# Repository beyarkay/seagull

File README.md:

# Conway's Game of Life (entirely in hardware)

> NOTE:
>
> This is a KiCAD project, don't expect GitHub to play especially well with it.

|   Back Copper Layer    |    Front Copper Layer    |
| :--------------------: | :----------------------: |
|  |  |

This project implements Conway's game of life, entirely in hardware. Many
existing attempts to do this fail (IMO) in one of several ways. The features of
this project are:

- All logic is computed via logic gates, no microcontrollers are used
- Each cell in the game of life is an independent PCB, and cells can be
  disconnected/connected at will

I am still busy optimising the design, but I have ordered and tested PCBs from
JLCPCB, the design and concept works.

|      Input/Output Headers      |
| :----------------------------: |
|              |
|       Sum-of-neighbours        |
|  |
|   Logic (should I be dead?)    |
|        |

# What is Conway's Game of Life?

(expand if you don't know what CGoL is)

<summary>
<details>
It is a cellular automaton on an infinite grid of square cells. Each cell is
either alive or dead. All cells update **simultaneously** in discrete ticks
based only on their eight adjacent neighbours (N, NE, E, SE, S, SW, W, NW). It
is usually called a **zero-player** game: you choose the starting pattern; the
rules determine everything after.

Rules per tick:

- exactly three live neighbours => the cell is alive next tick (birth or survival)
- exactly two live neighbours **and** the cell is currently alive => it stays alive
- any other neighbours count => the cell is dead next tick

This small rule set yields rich behaviour:

- Still lifes: patterns that do not change (e.g., block, beehive)
- Oscillators: patterns that repeat after N ticks (e.g., blinker, toad)
- Spaceships: patterns that translate over the grid (e.g., glider)
- Guns: patterns that periodically emit spaceships (e.g., Gosper glider gun)

Example of motion and emission:

There is a large taxonomy of creatures in CGoL, the [wiki][1] is comprehensive.

</details>
</summary>

# What is this project?

This project is a circuit board that implements Conway's game of life in pure
hardware using digital logic circuits. There is no Arduino, no code, no
microcontrollers, no "flashing". Just NOR gates. Each cell in Game of Life is a
completely independent PCB, and only has knowledge of it's eight immediate
neighbours. Physically connecting a grid of PCBs together will give you a
network of cells, and then you can run Game of Life.

|  Render of the front of the PCB   |  Render of the back of the PCB  |
| :-------------------------------: | :-----------------------------: |
|  |  |

As far as I can tell, nobody's done this before. There's been hardware
implementations of Life, but they all use microcontrollers and typically just
have one small grid that can't be extended (which seems lame IMO).

Each cell is about 35mm on a side and has an LED in the middle to indicate if
the cell is alive or dead. There's also two buttons: KILL and REVIVE that'll
force the state of the cell, so that you can initialise the game.

|    Two cells connected together     | Render of many cells connected together |
| :---------------------------------: | :-------------------------------------: |
|  |   |

I'm quite proud of this little thing. It's the first PCB I've designed and
overall it went really well. There were several fun engineering challenges with
routing information between cells and minimising the Game of Life logic to be
suitable for expression via NOR gates. My background is in the ideal perfect
world of computer science, and it has been very interesting learning PCB design
and making something that works in the real world against real constraints. I
strongly recommend anyone curious about it to give PCB design a go.

| It works! (cell in a testing jig, in the "alive" state) |
| :-----------------------------------------------------: |
|                     |

# Challenges/details

(I'm still writing this up and adding to this as I encounter new challenges)

## Routing information between cells

Each cell needs to know the state (alive/dead) of the eight cells surrounding
it. The four directly adjacent cells are easy, we can just have a pin & socket
poking out of the four edges of the boards. But the four diagonal cells are
trickier, because if we had diagonal pins & sockets then we wouldn't be able to
plug anything in.

The solution here is quite neat: you can route the information for diagonal
cells _through_ the directly adjacent cells. For example, to get state from the
top-left cell to the central cell, the state for the top-left cell will go
first to the left cell, and then to the central cell.

| Cell State is communicated via adjacent neighbours |
| :------------------------------------------------: |
|                                  |

## Implementing Game of Life via NOR circuits

(WIP)

## Calculating the neighbours sum

(WIP)

## Problems & frustrations

[you-live-like-this.meme]

Some notes from a software dev about pains in the electronic engineering world
that absolutely don't need to be there. It's kinda insane to me that some of
these problems still exist and don't have _any_ prospective solutions.

- PCB circuit "linting" basically doesn't exist, and could be a lot better.
- importing footprints is incredibly tedious and manual, not at all like `cargo
add random`.
- Insane that circuit manufacturers almost certainly have computer-readable
  descriptions of the behaviour of their chips but don't make that generally
  available. If you want to run "unit tests" on your circuit, you basically
  have to mock/re-define the behaviour of every chip you use. Which is a mammoth
  task if starting from scratch.
- The datasheet is the medium for communicating information about electrical
  components, but _there's no computer-readable format_. So you end up having
  to also find some footprints and schematics for the component (this
  information is in the datasheet, but computer's can't parse the
  images/diagrams).
- KiCAD is (mostly) a very capable piece of software. It could be better, but
  all my problems are "wants" rather than "needs", and I never explored the
  ecosystem of plugins that I believe dramatically improve the base experience.

To be clear: lots of these problems are "small" or "once-off" or solvable by
"just know this hack". But the whole culture in electronic engineering seems to
be to ignore the paper-cuts, while the culture amongst software engineers is
overwhelmingly the opposite. Software engineers are probably more guilty of
spending too _much_ time trying to automate every little inconvenience and
remove all manual steps from their once-a-year workflow. But the result of this
obsession is that most things are _able_ to be automated, and there's a
proliferation of adhered-to standards. Critically, being able to automate
things requires well-defined interfaces between different companies &
organisations across different countries. We tend to take this for granted in
software, especially amongst open-source. But electrical engineers remark that
certain automation steps are impossible because it requires coordination across
different suppliers on standards for representing information about components.
This is 100% a solved problem in software, and I'd never before realised what a
powerhouse the humble RFC is. The lack of a computer-readable datasheet for
electrical components is _insane_ to me, and ripe for automation via LLMs (if
not today, then in 5 years time).

# Next steps

Thanks to the Albert, Karel, Dirk S., Armand, and the other devs at CubeSpace
for advice, and various anime-profile-picture twitter accounts in the PCB Book
Club for schematic/PCB reviews)

[1]: https://conwaylife.com/wiki/Main_Page

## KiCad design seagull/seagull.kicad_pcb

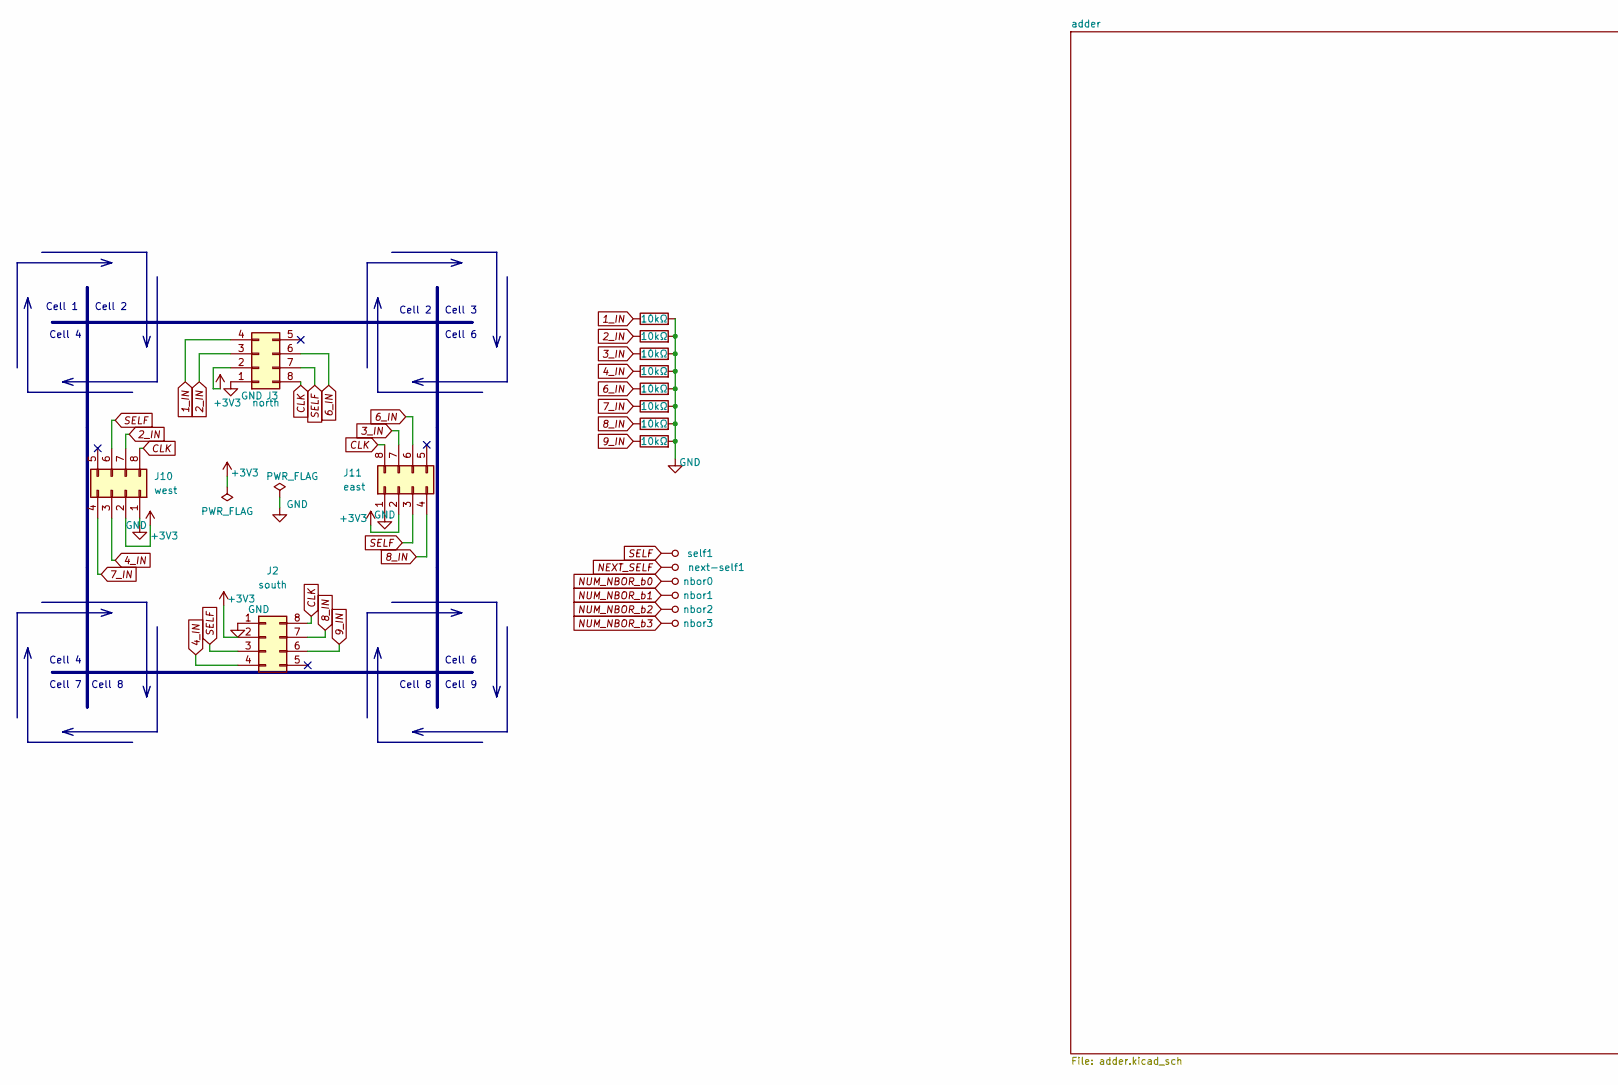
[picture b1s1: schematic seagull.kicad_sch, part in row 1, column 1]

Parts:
J2: south; PinHeader_2x04_P2.54mm_Horizontal
J3: north; PinSocket_2x04_P2.54mm_Horizontal
J10: west; PinSocket_2x04_P2.54mm_Horizontal
J11: east; PinHeader_2x04_P2.54mm_Horizontal
R1, R2, R3, R4, R5, R6, R7, R8: 10kΩ; R_1206_3216Metric_Pad1.30x1.75mm_HandSolder
nbor0, nbor1, nbor2, nbor3: 5011; TestPoint_Pad_D1.0mm; MPN 5011; Digi-Key_PN 36-5011-ND
next-self1: 5011; TestPoint_Pad_D1.0mm; MPN 5011; Digi-Key_PN 36-5011-ND
self1: 5011; TestPoint_Pad_D1.0mm; MPN 5011; Digi-Key_PN 36-5011-ND

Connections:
1_IN: J3.4, R1.1; also elsewhere on the board
2_IN: J3.3, J10.7, R2.1; also elsewhere on the board
3_IN: J11.7, R3.1; also elsewhere on the board
4_IN: J2.4, J10.3, R4.1; also elsewhere on the board
6_IN: J3.6, J11.6, R5.1; also elsewhere on the board
7_IN: J10.4, R6.1; also elsewhere on the board
8_IN: J2.7, J11.4, R7.1; also elsewhere on the board
9_IN: J2.6, R8.1; also elsewhere on the board
CLK: J2.8, J3.8, J10.8, J11.8; also elsewhere on the board
GND: J2.1, J3.1, J10.1, J11.1, R1.2, R2.2, R3.2, R4.2, R5.2, R6.2, R7.2, R8.2; also elsewhere on the board
NEXT_SELF: next-self1.1; also elsewhere on the board
NUM_NBOR_b0: nbor0.1; also elsewhere on the board
NUM_NBOR_b1: nbor1.1; also elsewhere on the board
NUM_NBOR_b2: nbor2.1; also elsewhere on the board
NUM_NBOR_b3: nbor3.1; also elsewhere on the board
SELF: J2.3, J3.7, J10.6, J11.3, self1.1; also elsewhere on the board

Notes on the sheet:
Cell 4
Cell 3
Cell 6
Cell 8
Cell 7
Cell 9
Cell 1
Cell 2

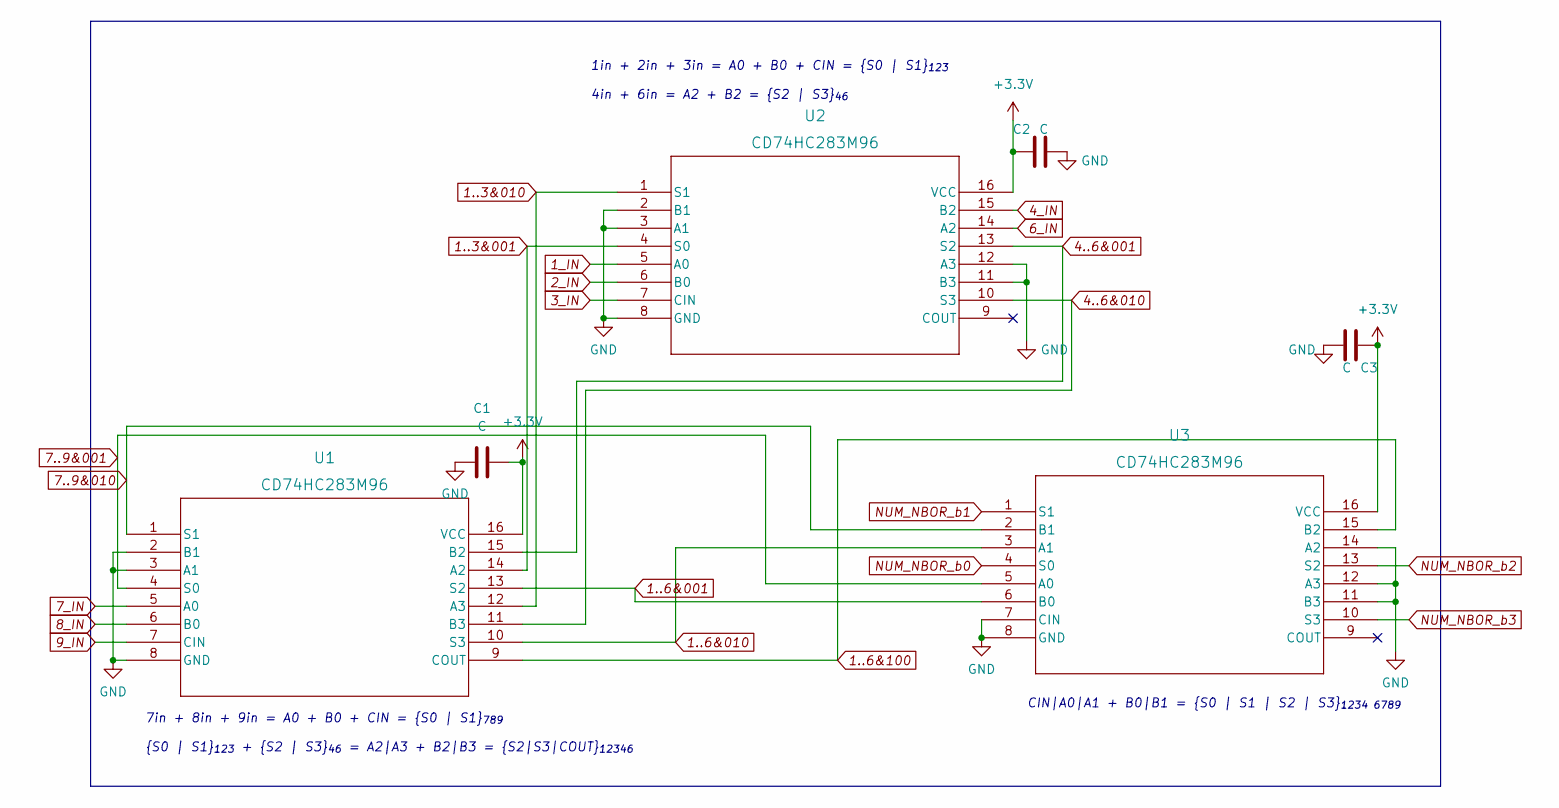
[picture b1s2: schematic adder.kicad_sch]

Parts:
C1, C2, C3: C; C_1206_3216Metric_Pad1.33x1.80mm_HandSolder
U1, U2, U3: CD74HC283M96; CD74HC283M96_4bit_adder_D16-L

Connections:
1..3&001: U1.14 (A2), U2.4 (S0)
1..3&010: U1.12 (A3), U2.1 (S1)
1..6&001: U1.13 (S2), U3.6 (B0)
1..6&010: U1.10 (S3), U3.3 (A1)
1..6&100: U1.9 (COUT), U3.15 (B2)
1_IN: U2.5 (A0); also elsewhere on the board
2_IN: U2.6 (B0); also elsewhere on the board
3_IN: U2.7 (CIN); also elsewhere on the board
4..6&001: U1.15 (B2), U2.13 (S2)
4..6&010: U1.11 (B3), U2.10 (S3)
4_IN: U2.15 (B2); also elsewhere on the board
6_IN: U2.14 (A2); also elsewhere on the board
7..9&001: U1.4 (S0), U3.5 (A0)
7..9&010: U1.1 (S1), U3.2 (B1)
7_IN: U1.5 (A0); also elsewhere on the board
8_IN: U1.6 (B0); also elsewhere on the board
9_IN: U1.7 (CIN); also elsewhere on the board
GND: C1.1, C2.2, C3.2, U1.2 (B1), U1.3 (A1), U1.8 (GND), U2.2 (B1), U2.3 (A1), U2.8 (GND), U2.11 (B3), U2.12 (A3), U3.7 (CIN), U3.8 (GND), U3.11 (B3), U3.12 (A3), U3.14 (A2); also elsewhere on the board
NUM_NBOR_b0: U3.4 (S0); also elsewhere on the board
NUM_NBOR_b1: U3.1 (S1); also elsewhere on the board
NUM_NBOR_b2: U3.13 (S2); also elsewhere on the board
NUM_NBOR_b3: U3.10 (S3); also elsewhere on the board

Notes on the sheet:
CIN|A0|A1 + B0|B1 = {S0 | S1 | S2 | S3}_{1234 6789}
1in + 2in + 3in = A0 + B0 + CIN = {S0 | S1}_{123} 4in + 6in = A2 + B2 = {S2 | S3}_{46}
7in + 8in + 9in = A0 + B0 + CIN = {S0 | S1}_{789} {S0 | S1}_{123} + {S2 | S3}_{46} = A2|A3 + B2|B3 = {S2|S3|COUT}_{12346}

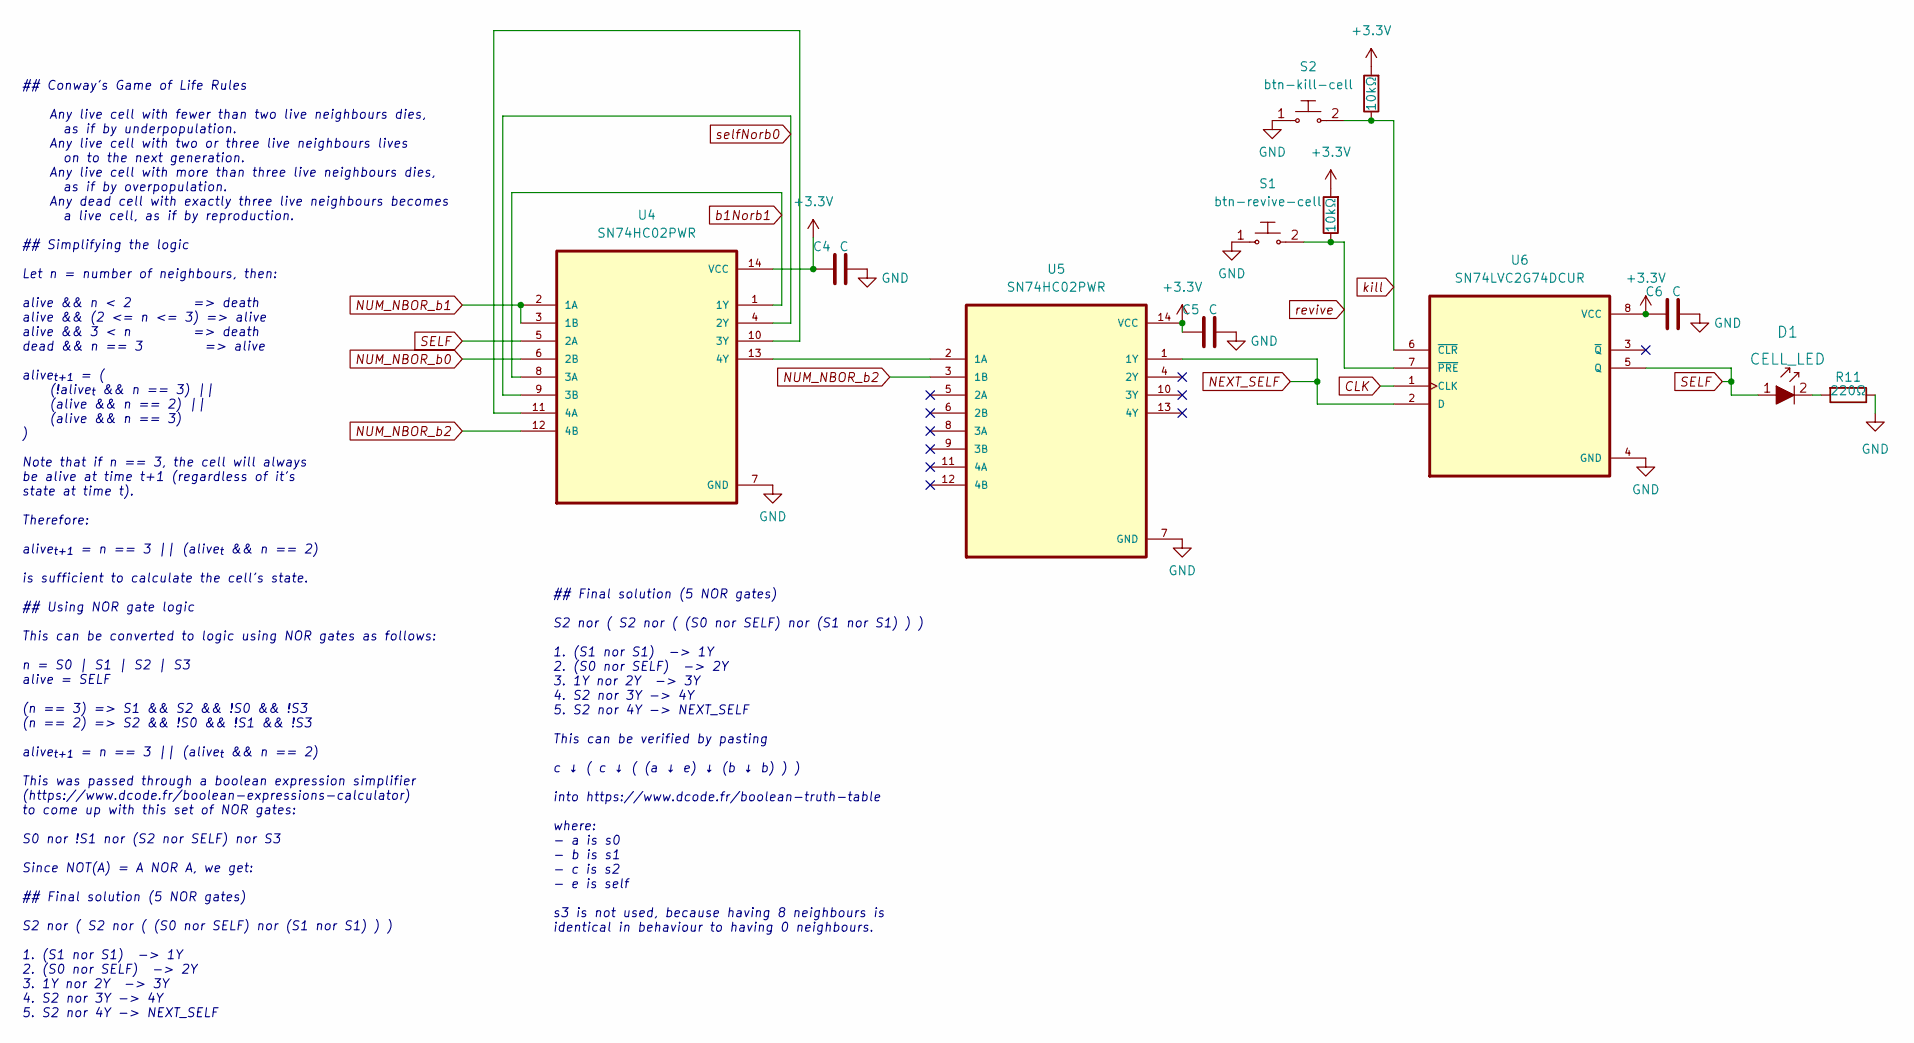
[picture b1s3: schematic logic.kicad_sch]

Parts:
C4, C5, C6: C; C_1206_3216Metric_Pad1.33x1.80mm_HandSolder
D1: CELL_LED; 1206; MPN LTST-C171KRKT; Digi-Key_PN 160-1427-1-ND
R9, R10: 10kΩ; R_1206_3216Metric_Pad1.30x1.75mm_HandSolder
R11: 220Ω; R_1206_3216Metric_Pad1.30x1.75mm_HandSolder
S1: btn-revive-cell; SW_1825910-6-btn; MPN GPTS203211B; Digi-Key_PN CW181-ND
S2: btn-kill-cell; SW_1825910-6-btn; MPN GPTS203211B; Digi-Key_PN CW181-ND
U4, U5: SN74HC02PWR; SN74HC02PWR_NOR_4CH_2-INP
U6: SN74LVC2G74DCUR; SN74LVC2G74DCUR_d-flip-flop

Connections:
CLK: U6.1 (CLK); also elsewhere on the board
GND: C4.2, C5.2, C6.2, R11.1, S1.1, S2.1, U4.7 (GND), U5.7 (GND), U6.4 (GND); also elsewhere on the board
NEXT_SELF: U5.1 (1Y), U6.2 (D); also elsewhere on the board
NUM_NBOR_b0: U4.6 (2B); also elsewhere on the board
NUM_NBOR_b1: U4.2 (1A), U4.3 (1B); also elsewhere on the board
NUM_NBOR_b2: U4.12 (4B), U5.3 (1B); also elsewhere on the board
unnamed: D1.2, R11.2
unnamed: U4.10 (3Y), U4.11 (4A)
unnamed: U4.13 (4Y), U5.2 (1A)
SELF: D1.1, U4.5 (2A), U6.5 (Q); also elsewhere on the board
b1Norb1: U4.1 (1Y), U4.8 (3A)
kill: R10.1, S2.2, U6.6 (~CLR)
revive: R9.1, S1.2, U6.7 (~PRE)
selfNorb0: U4.4 (2Y), U4.9 (3B)

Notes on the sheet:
## Conway's Game of Life Rules Any live cell with fewer than two live neighbours dies, as if by underpopulation. Any live cell with two or three live neighbours lives on to the next generation. Any live cell with more than three live neighbours dies, as if by overpopulation. Any dead cell with exac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
## Final solution (5 NOR gates) S2 nor ( S2 nor ( (S0 nor SELF) nor (S1 nor S1) ) ) 1. (S1 nor S1) -> 1Y 2. (S0 nor SELF) -> 2Y 3. 1Y nor 2Y -> 3Y 4. S2 nor 3Y -> 4Y 5. S2 nor 4Y -> NEXT_SELF This can be verified by pasting c ↓ ( c ↓ ( (a ↓ e) ↓ (b ↓ b) ) ) into https://www.dcode.fr/boolean-truth-t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

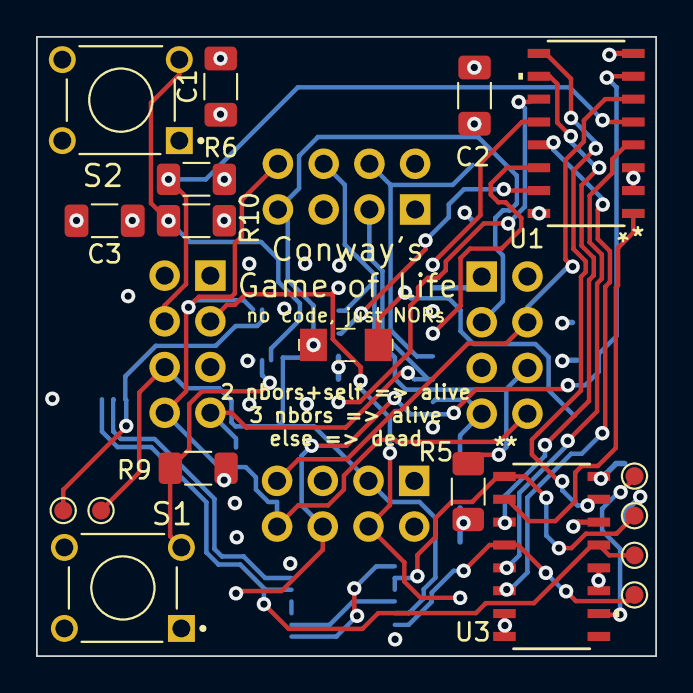
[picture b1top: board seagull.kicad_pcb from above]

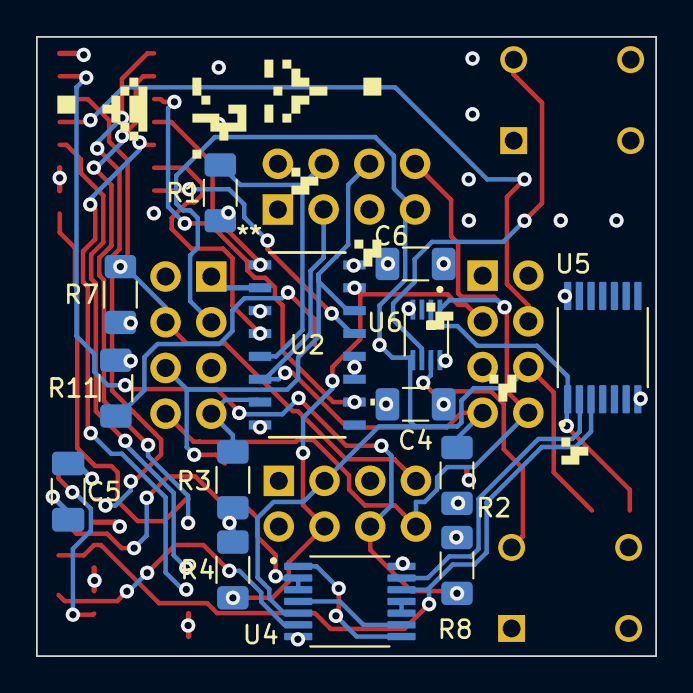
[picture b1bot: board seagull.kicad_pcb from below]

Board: 4 copper layers, 34.4 x 34.4 mm, 36 parts (14 on the bottom side), 33 nets.

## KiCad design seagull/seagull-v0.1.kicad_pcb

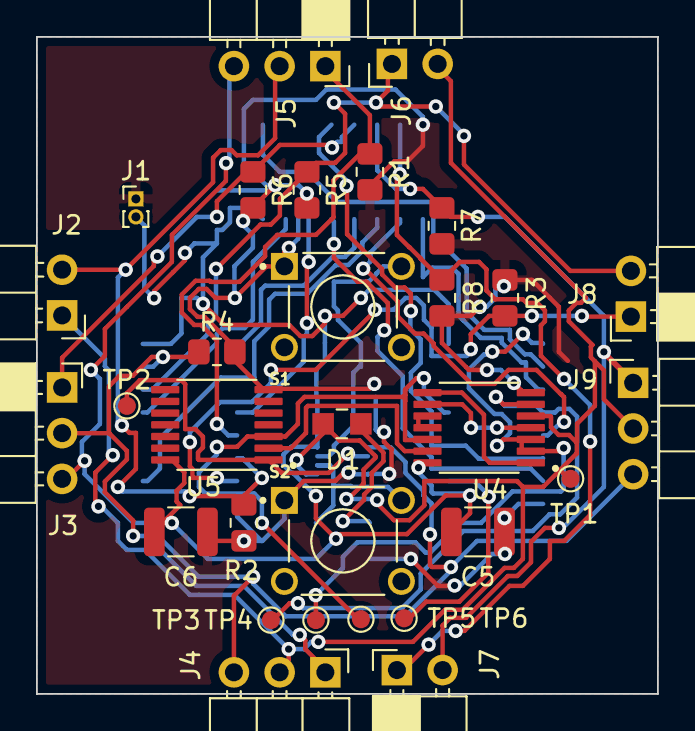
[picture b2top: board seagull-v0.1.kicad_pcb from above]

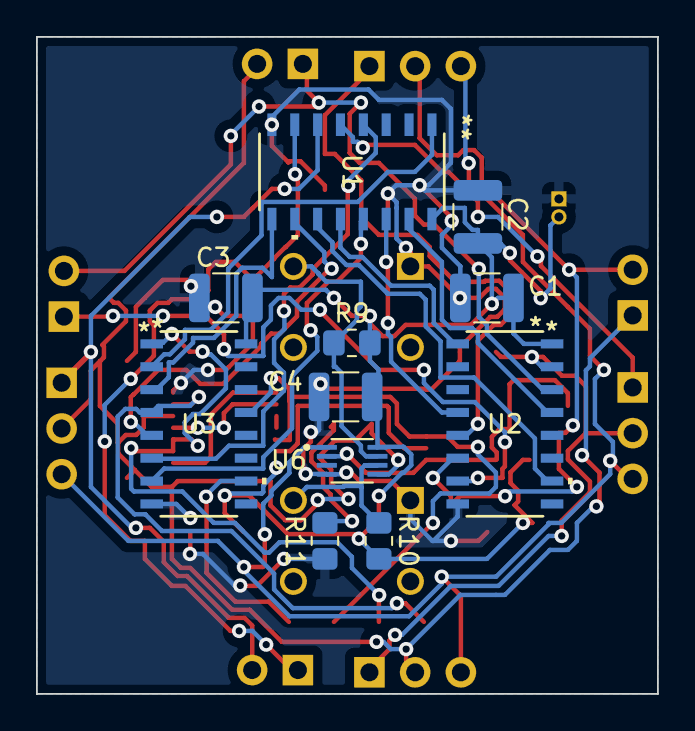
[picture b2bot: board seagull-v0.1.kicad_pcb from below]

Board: 2 copper layers, 34.5 x 36.5 mm, 41 parts (11 on the bottom side), 33 nets.

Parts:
C1, C2, C3, C4, C5, C6: C; C_1210_3225Metric
D1: CELL_LED; 0805
J1: Power In; PinHeader_1x02_P1.00mm_Vertical
J2: W; PinHeader_1x02_P2.54mm_Horizontal
J3: W; PinSocket_1x03_P2.54mm_Horizontal
J4: S; PinHeader_1x03_P2.54mm_Horizontal
J5: N; PinSocket_1x03_P2.54mm_Horizontal
J6: N; PinHeader_1x02_P2.54mm_Horizontal
J7: S; PinSocket_1x02_P2.54mm_Horizontal
J8: E; PinSocket_1x02_P2.54mm_Horizontal
J9: E; PinHeader_1x03_P2.54mm_Horizontal
R1, R2, R3, R4, R5, R6, R7, R8, R9, R10: 10kΩ; R_0805_2012Metric_Pad1.20x1.40mm_HandSolder
R11: 220Ω; R_0805_2012Metric_Pad1.20x1.40mm_HandSolder
S1: btn-revive-cell; SW_1825910-6-btn
S2: btn-kill-cell; SW_1825910-6-btn
TP1, TP2, TP3, TP4, TP5, TP6: 5011; TestPoint_Pad_D1.0mm
U1, U2, U3: CD74HC283M96; CD74HC283M96_4bit_adder_D16-L
U4, U5: SN74HC02PWR; SN74HC02PWR_NOR_4CH_2-INP
U6: SN74LVC2G74DCUR; SN74LVC2G74DCUR_d-flip-flop

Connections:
1_IN: J5.1 (1-from-2), R1.1, U2.5 (A0)
2_IN: J2.2 (2-to-4), J5.2 (2-from-2), R2.1, U2.6 (B0)
3_IN: J8.1 (3-from-6), R3.1, U2.7 (CIN)
4_IN: J3.2 (4-from-4), J4.1 (4-to-8), R4.1, U2.15 (B2)
6_IN: J6.1 (6-to-2), J8.2 (6-from-6), R5.1, U2.14 (A2)
7_IN: J3.1 (7-from-4), R6.1, U1.5 (A0)
8_IN: J7.2 (8-from-8), J9.1 (8-to-6), R7.1, U1.6 (B0)
9_IN: J7.1 (9-from-8), R8.1, U1.7 (CIN)
+3V3: C1.2, C2.1, C3.1, C4.1, C5.1, C6.1, J1.2, R9.2, R10.2, U1.16 (VCC), U2.16 (VCC), U3.16 (VCC), U4.14 (VCC), U5.14 (VCC), U6.8 (VCC)
CLK: J3.3 (clk-from-4), J4.3 (clk-to-8), J5.3 (clk-from-2), J9.3 (clk-to-6), U6.1 (CLK)
GND: C1.1, C2.2, C3.2, C4.2, C5.2, C6.2, J1.1, R1.2, R2.2, R3.2, R4.2, R5.2, R6.2, R7.2, R8.2, R11.1, S1.1, S2.1, U1.8 (GND), U2.8 (GND), U3.8 (GND), U4.7 (GND), U5.7 (GND), U6.4 (GND)
NEXT_SELF: TP2.1, U5.1 (1Y), U6.2 (D)
NUM_NBOR_b0: TP3.1, U3.4 (S0), U4.6 (2B)
NUM_NBOR_b1: TP4.1, U3.1 (S1), U4.2 (1A), U4.3 (1B)
NUM_NBOR_b2: TP5.1, U3.13 (S2), U4.12 (4B), U5.3 (1B)
NUM_NBOR_b3: TP6.1, U3.10 (S3)
unnamed: D1.2, R11.2
unnamed: R9.1, S1.2, U6.7 (~PRE)
unnamed: R10.1, S2.2, U6.6 (~CLR)
unnamed: U1.1 (S1), U3.2 (B1)
unnamed: U1.4 (S0), U3.6 (B0)
unnamed: U1.9 (COUT), U3.3 (A1)
unnamed: U1.10 (S3), U3.5 (A0)
unnamed: U1.11 (B3), U2.10 (S3)
unnamed: U1.12 (A3), U2.1 (S1)
unnamed: U1.13 (S2), U3.7 (CIN)
unnamed: U1.14 (A2), U2.4 (S0)
unnamed: U1.15 (B2), U2.13 (S2)
unnamed: U4.1 (1Y), U4.8 (3A)
unnamed: U4.4 (2Y), U4.9 (3B)
unnamed: U4.10 (3Y), U4.11 (4A)
unnamed: U4.13 (4Y), U5.2 (1A)
SELF: D1.1, J2.1 (self-to-4), J4.2 (self-to-8), J6.2 (self-to-2), J9.2 (self-to-6), TP1.1, U4.5 (2A), U6.5 (Q)

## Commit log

2025-09-28 Add .gitignore
2025-09-28 Add initial README.md
2025-09-28 add images
2025-09-28 Update readme, add images
2025-09-28 Udapte readme with images
2025-09-28 Add more images
2025-09-28 ¯\_(ツ)_/¯ Final commit, ready for tagging
